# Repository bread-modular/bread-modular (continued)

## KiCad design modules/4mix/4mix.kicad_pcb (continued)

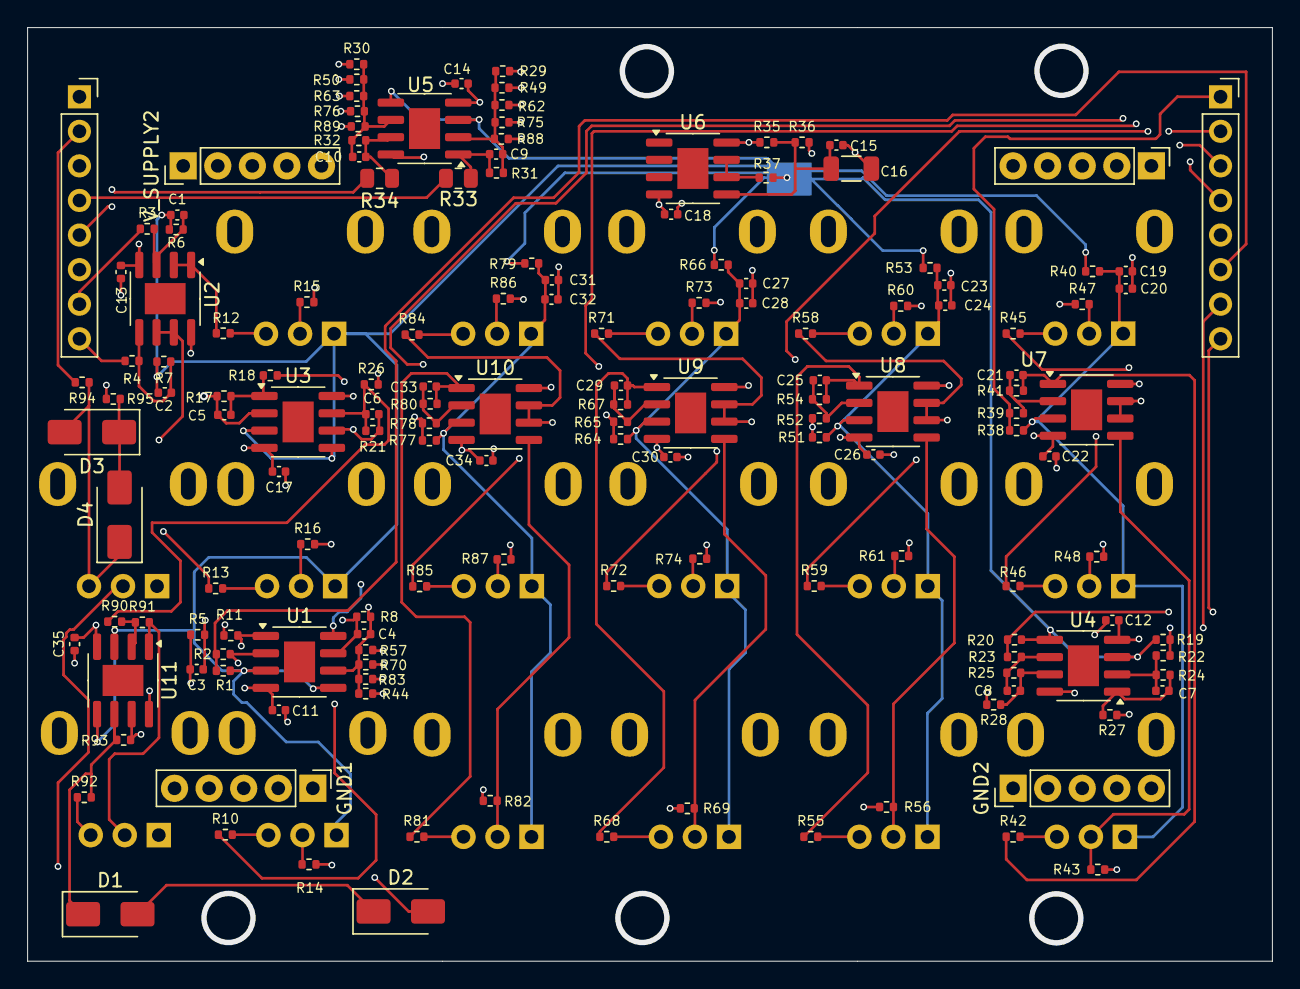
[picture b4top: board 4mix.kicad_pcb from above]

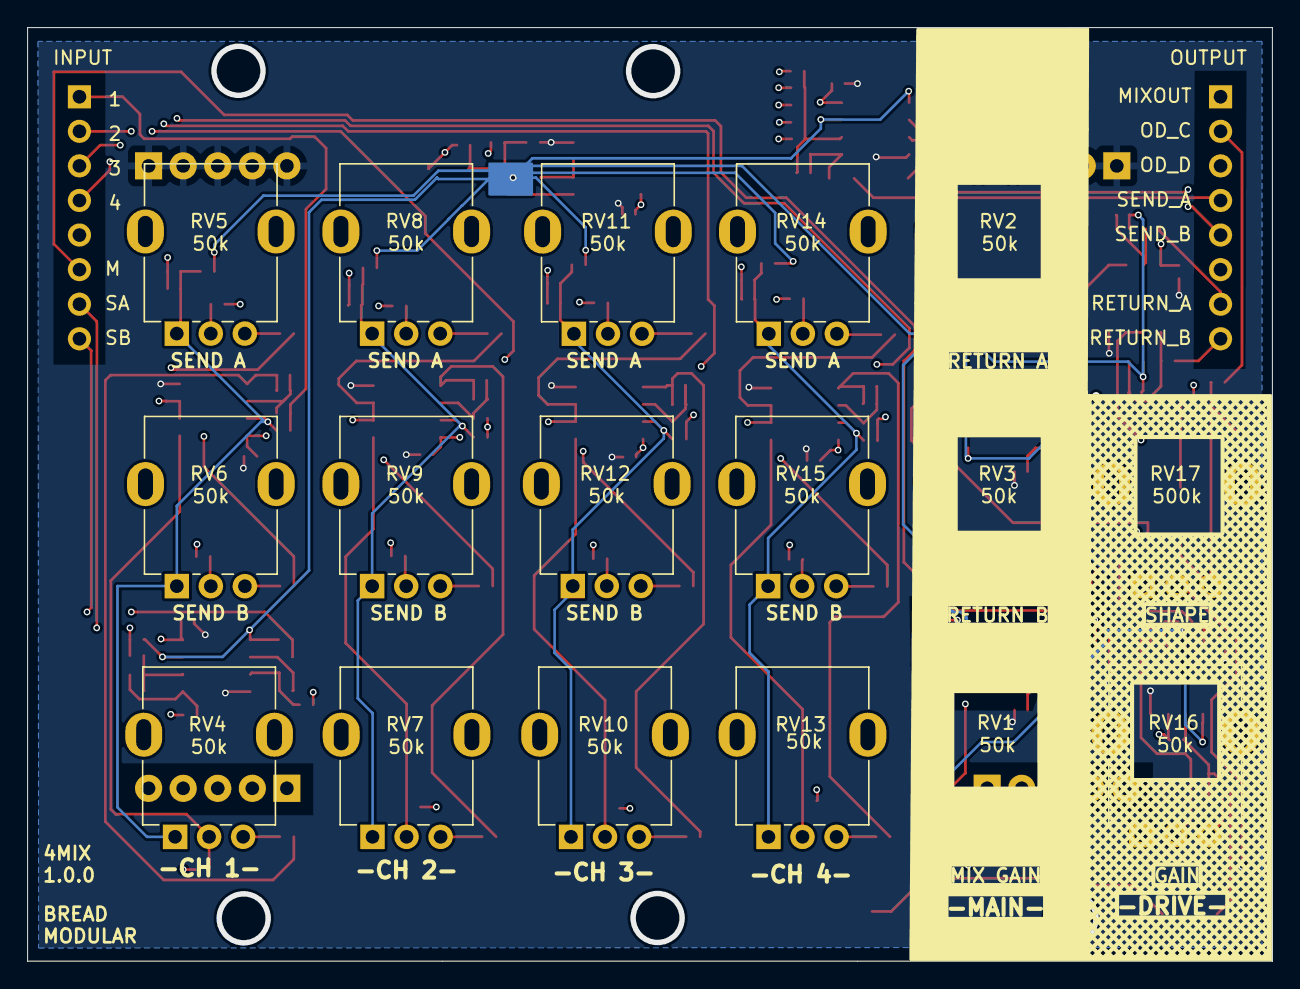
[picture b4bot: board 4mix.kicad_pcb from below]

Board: 4 copper layers, 91.4 x 68.6 mm, 167 parts (17 on the bottom side), 107 nets.

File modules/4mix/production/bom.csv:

Designator,Footprint,Quantity,Value,LCSC Part #
"C1, C2",0402,2,100pf,
"C10, C21, C25, C29, C3, C33, C4, C5, C6, C7, C8, C9",0402,12,47pf,
"C11, C12, C13, C14, C15, C17, C18, C20, C22, C24, C26, C28, C30, C32, C34, C35",0402,16,0.1uf,
C16,1206,1,100uf,
"C19, C23, C27, C31",0402,4,10uf,
"D1, D2, D3",D_SMA,3,SS14,
D4,D_SMA,1,SS210,
"GND1, GND2, V_SUPPLY1, V_SUPPLY2",Power_Connector,4,Conn_01x05_Pin,
"INPUT1, OUTPUT1",PinSocket_1x08_P2.54mm_Vertical,2,Conn_01x05_Socket,
"R1, R19, R20, R38, R51, R6, R64, R7, R77",0402,9,1M,
"R10, R12, R13, R27, R28, R40, R42, R43, R45, R46, R47, R48, R53, R55, R56, R58, R59, R60, R61, R66, R68, R69, R71, R72, R73, R74, R79, R81, R82, R84, R85, R86, R87",0402,33,100,
"R11, R14, R15, R16, R17, R18, R2, R21, R22, R23, R24, R25, R29, R30, R31, R32, R39, R41, R44, R49, R5, R50, R52, R54, R57, R62, R63, R65, R67, R70, R75, R76, R78, R8, R80, R83, R88, R89",0402,38,56k,
"R26, R92, R94, R95",0402,4,1k,
"R3, R35, R36, R4",0402,4,10k,
"R33, R34",0805,2,330,
R37,0402,1,10,
"R90, R91",0402,2,100k,
R93,0402,1,51k,
"RV1, RV10, RV11, RV12, RV13, RV14, RV15, RV16, RV2, RV3, RV4, RV5, RV6, RV7, RV8, RV9",Potentiometer_RV09,16,50k,
RV17,Potentiometer_RV09,1,500k,
"U1, U10, U11, U2, U3, U4, U5, U6, U7, U8, U9",SOIC-8-1EP_3.9x4.9mm_P1.27mm_EP2.29x3mm,11,MCP6002-xSN,

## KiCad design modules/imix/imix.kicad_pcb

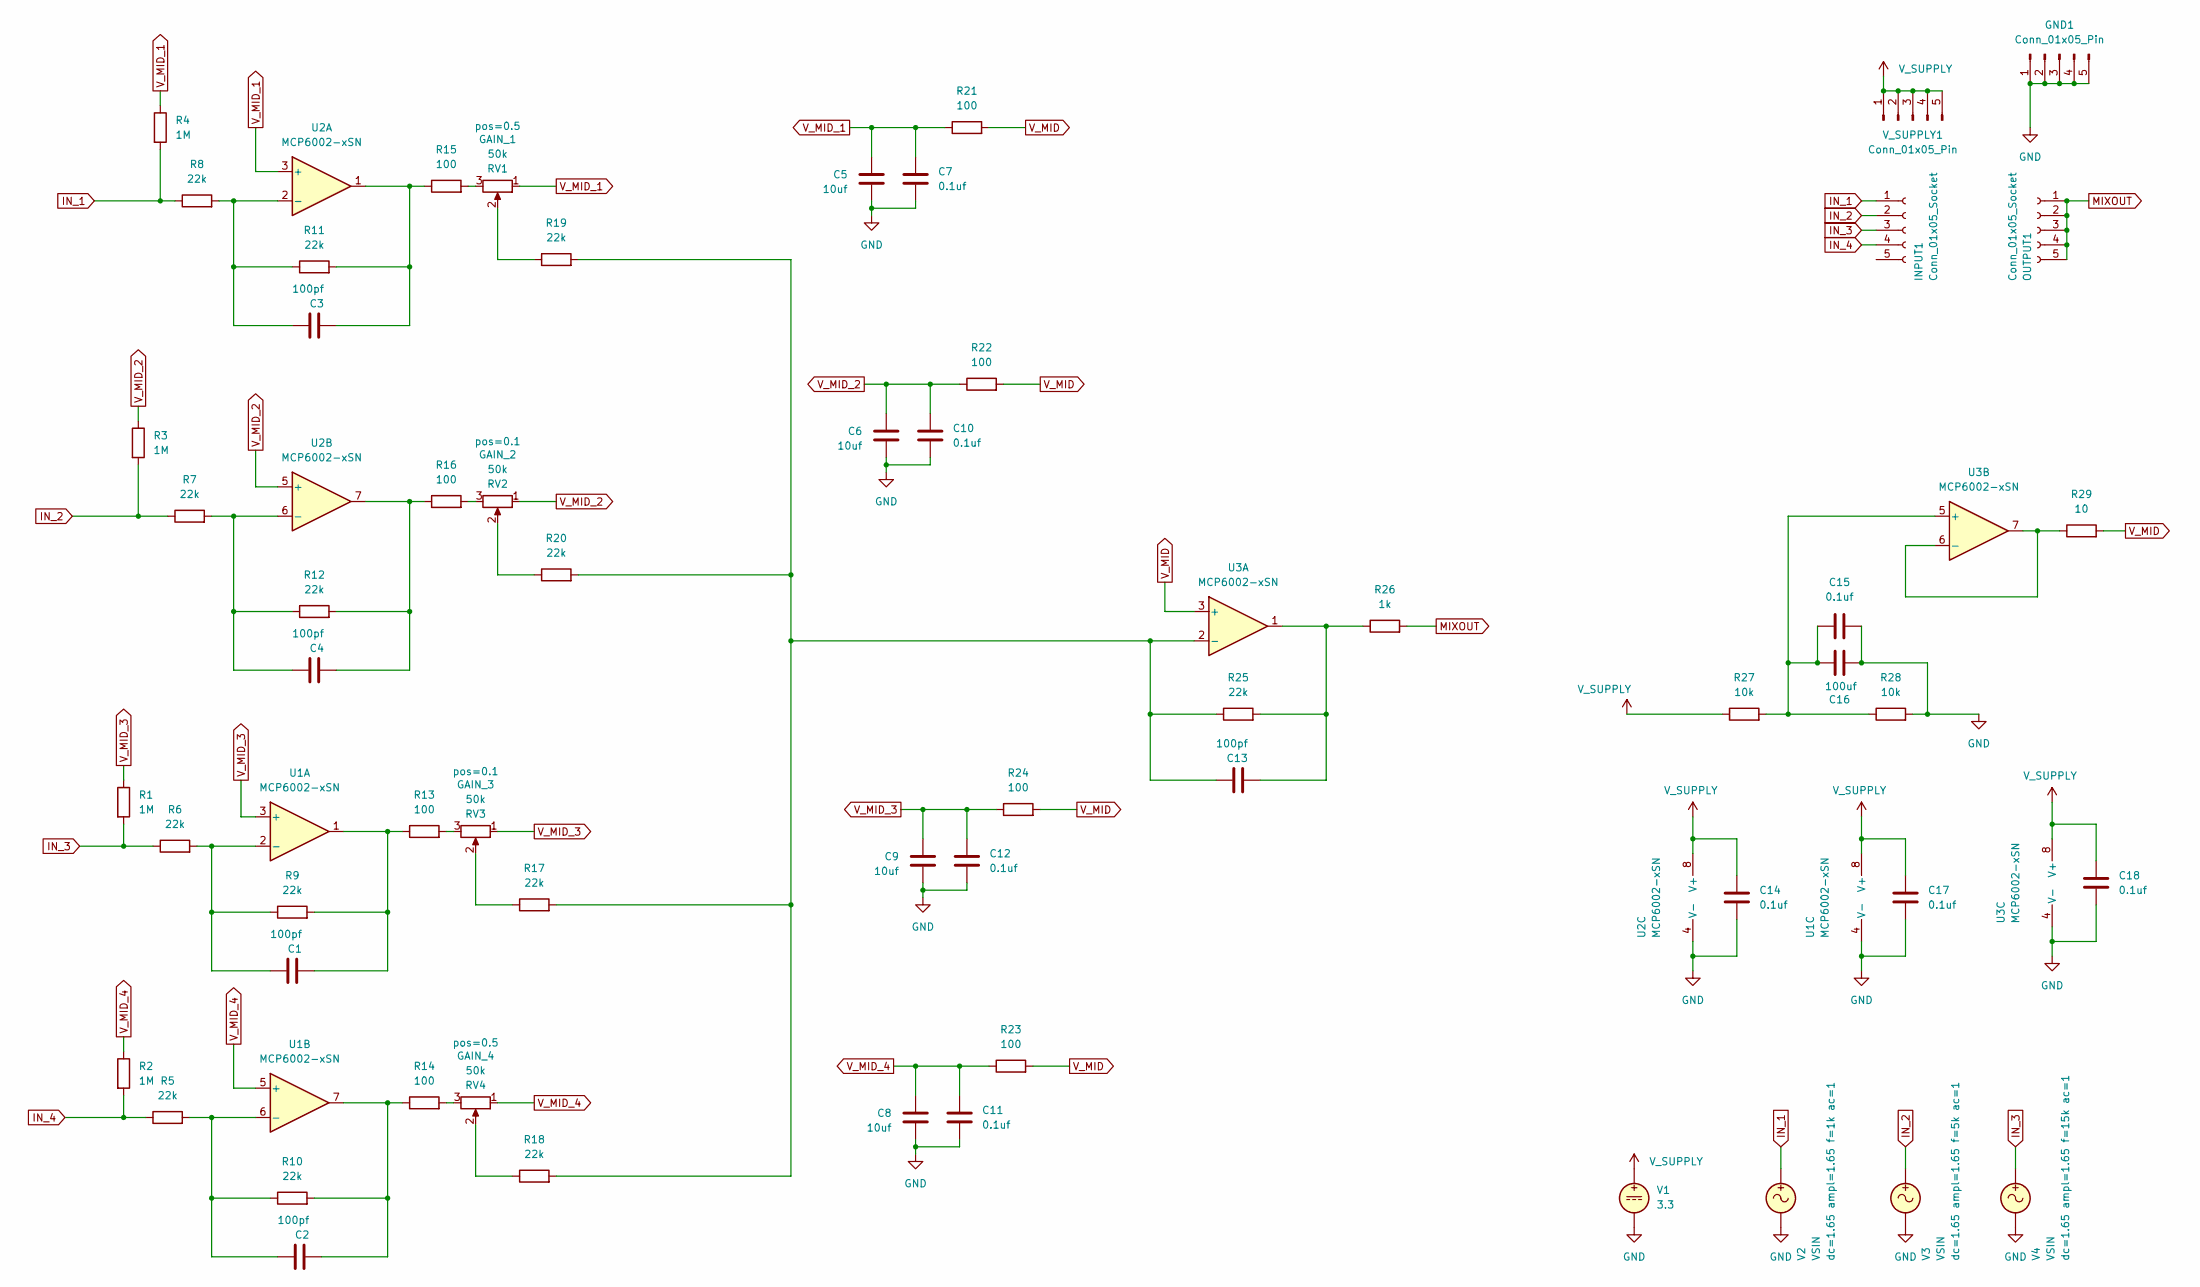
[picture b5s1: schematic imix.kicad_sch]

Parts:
C1, C2, C3, C4, C13: 100pf; C_0402_1005Metric
C5, C6, C8, C9: 10uf; C_0402_1005Metric
C7, C10, C11, C12, C14, C15, C17, C18: 0.1uf; C_0402_1005Metric
C16: 100uf; C_1206_3216Metric
GND1: Conn_01x05_Pin; Power_Connector
INPUT1: Conn_01x05_Socket; PinSocket_1x05_P2.54mm_Vertical
OUTPUT1: Conn_01x05_Socket; PinSocket_1x05_P2.54mm_Vertical
R1, R2, R3, R4: 1M; R_0402_1005Metric
R5, R6, R7, R8, R9, R10, R11, R12, R17, R18, R19, R20, R25: 22k; R_0402_1005Metric
R13, R14, R15, R16, R21, R22, R23, R24: 100; R_0402_1005Metric
R26: 1k; R_0402_1005Metric
R27, R28: 10k; R_0402_1005Metric
R29: 10; R_0402_1005Metric
RV1, RV2, RV3, RV4: 50k; Potentiometer_RV09
U1, U2, U3: MCP6002-xSN; SOIC-8-1EP_3.9x4.9mm_P1.27mm_EP2.29x3mm
V1: 3.3
V2, V3, V4: VSIN
V_SUPPLY1: Conn_01x05_Pin; Power_Connector

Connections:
GND: C5.2, C6.2, C7.2, C8.2, C9.2, C10.2, C11.2, C12.2, C14.2, C15.2, C16.2, C17.2, C18.2, GND1.1, GND1.2, GND1.3, GND1.4, GND1.5, R28.2, U1.4 (V-), U2.4 (V-), U3.4 (V-), V1.2, V2.2, V3.2, V4.2
IN_1: INPUT1.1, R4.2, R8.1, V2.1
IN_2: INPUT1.2, R3.2, R7.1, V3.1
IN_3: INPUT1.3, R1.2, R6.1, V4.1
IN_4: INPUT1.4, R2.2, R5.1
MIXOUT: OUTPUT1.1, OUTPUT1.2, OUTPUT1.3, OUTPUT1.4, OUTPUT1.5, R26.2
unnamed: C1.2, R9.2, R13.1, U1.1
unnamed: C2.2, R10.2, R14.1, U1.7
unnamed: C3.2, R11.2, R15.1, U2.1
unnamed: C4.2, R12.2, R16.1, U2.7
unnamed: C13.2, R25.2, R26.1, U3.1
unnamed: R13.2, RV3.3
unnamed: R14.2, RV4.3
unnamed: R15.2, RV1.3
unnamed: R16.2, RV2.3
unnamed: R17.1, RV3.2
unnamed: R18.1, RV4.2
unnamed: R19.1, RV1.2
unnamed: R20.1, RV2.2
unnamed: C1.1, R6.2, R9.1, U1.2 (-)
unnamed: C2.1, R5.2, R10.1, U1.6 (-)
unnamed: C3.1, R8.2, R11.1, U2.2 (-)
unnamed: C4.1, R7.2, R12.1, U2.6 (-)
unnamed: C13.1, R17.2, R18.2, R19.2, R20.2, R25.1, U3.2 (-)
unnamed: C15.1, C16.1, R27.2, R28.1, U3.5 (+)
unnamed: R29.1, U3.6 (-), U3.7
V_MID: R21.2, R22.2, R23.2, R24.2, R29.2, U3.3 (+)
V_MID_1: C5.1, C7.1, R4.1, R21.1, RV1.1, U2.3 (+)
V_MID_2: C6.1, C10.1, R3.1, R22.1, RV2.1, U2.5 (+)
V_MID_3: C9.1, C12.1, R1.1, R24.1, RV3.1, U1.3 (+)
V_MID_4: C8.1, C11.1, R2.1, R23.1, RV4.1, U1.5 (+)
V_SUPPLY: C14.1, C17.1, C18.1, R27.1, U1.8 (V+), U2.8 (V+), U3.8 (V+), V1.1, V_SUPPLY1.1, V_SUPPLY1.2, V_SUPPLY1.3, V_SUPPLY1.4, V_SUPPLY1.5

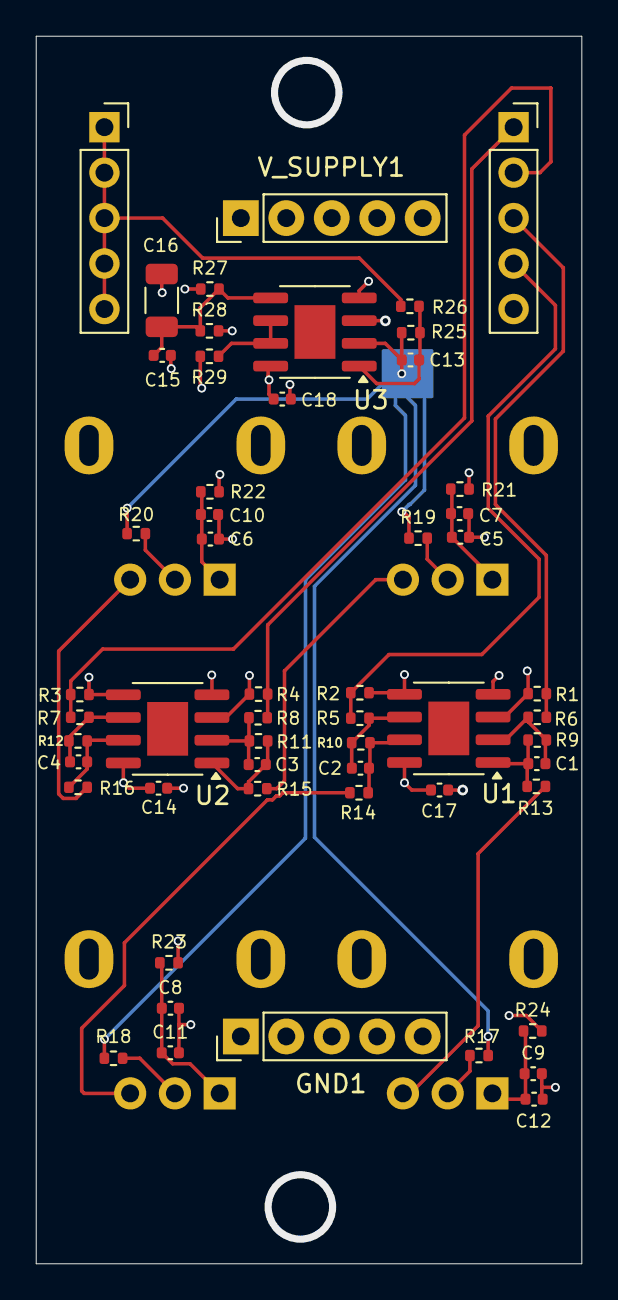
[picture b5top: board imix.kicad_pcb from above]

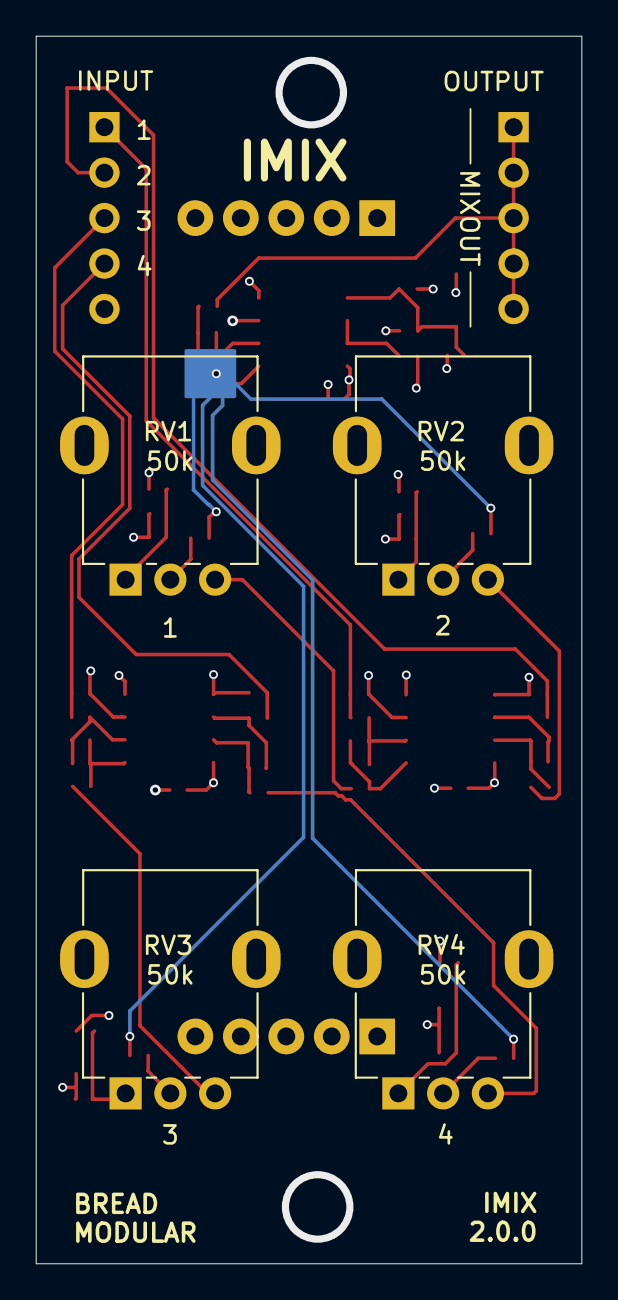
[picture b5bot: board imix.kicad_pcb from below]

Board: 4 copper layers, 30.5 x 68.6 mm, 58 parts (4 on the bottom side), 32 nets.

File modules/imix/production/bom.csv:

Designator,Footprint,Quantity,Value,LCSC Part #
"C1, C13, C2, C3, C4",0402,5,100pf,
"C10, C11, C12, C14, C15, C17, C18, C7",0402,8,0.1uf,
C16,1206,1,100uf,
"C5, C6, C8, C9",0402,4,10uf,
"GND1, V_SUPPLY1",Power_Connector,2,Conn_01x05_Pin,
"INPUT1, OUTPUT1",PinSocket_1x05_P2.54mm_Vertical,2,Conn_01x05_Socket,
"R1, R2, R3, R4",0402,4,1M,
"R10, R11, R12, R17, R18, R19, R20, R25, R5, R6, R7, R8, R9",0402,13,22k,
"R13, R14, R15, R16, R21, R22, R23, R24",0402,8,100,
R26,0402,1,1k,
"R27, R28",0402,2,10k,
R29,0402,1,10,
"RV1, RV2, RV3, RV4",Potentiometer_RV09,4,50k,
"U1, U2, U3",SOIC-8-1EP_3.9x4.9mm_P1.27mm_EP2.29x3mm,3,MCP6002-xSN,

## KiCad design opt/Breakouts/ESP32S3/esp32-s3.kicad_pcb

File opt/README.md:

# KiCad footprint libraries

`fp-lib-table` is the single project-specific footprint library table for all
Bread Modular KiCad projects, including deprecated modules and breakout boards.
Edit it here, not separately in each project. Existing library nicknames are
preserved, including the historical `BreadModular_Panalize` spelling and the
RP2350 breakout's `RP2350_60QFN_minimal` library.

Each project directory contains two **relative symlinks**:

- `fp-lib-table` → this shared `opt/fp-lib-table` file.
- `footprints` → `opt/footprints`, a directory of symlinks to the actual libraries.

The table uses `${KIPRJMOD}/footprints/<library>.pretty`. The `footprints` link
makes this work at any project depth without hard-coded checkout paths or
machine-wide KiCad environment variables. Linking to the library-only directory
also avoids directory cycles through the projects under `opt/Breakouts`.
Standard KiCad libraries continue to come from KiCad's global library table.
Custom symbol-library configuration is unchanged.

## Workspace setup

`workspace_init.sh /path/to/original/checkout` copies **all** submodules listed in
`.gitmodules`, including the four footprint-library submodules and the firmware
library. Tracked libraries and symlinks already arrive with the Git worktree.

- Setup never clones, fetches, or falls back to the network.
- Each copy includes private Git metadata and objects; no hardlinks or Git links
  back to the original checkout are used. Local source changes are copied too.
- Rerunning setup leaves initialized destinations (and their edits) untouched.
- Missing source checkouts or nonempty uninitialized destinations fail with an
  actionable error rather than fetching or overwriting files.
- Sources must be ordinary initialized submodules, not linked worktrees or
  repositories borrowing objects via Git alternates.

On a fresh main checkout, explicitly initialize submodules once before creating
workspaces: `git submodule update --init --recursive`. This manual bootstrap may
access the network; workspace creation itself does not.

## Adding a project

Create both symlinks next to its `.kicad_pro` file, adjusting the relative paths
for its depth. For example, from the repository root:

```sh
ln -s ../../opt/fp-lib-table modules/new-module/fp-lib-table
ln -s ../../opt/footprints modules/new-module/footprints
```

To add a library, add its symlink under `opt/footprints` and its entry to
`opt/fp-lib-table`. Existing projects immediately share the new entry. Reopen
KiCad if it has cached the old library table.

## Verification

From the repository root, with local submodules initialized:

```sh
python3 tests/test_workspace_init.py
# Optional: test copying the original checkout's .git-file-based submodules.
python3 tests/test_workspace_init.py /path/to/original/checkout

# Use a Python interpreter with KiCad's pcbnew module installed.
/usr/bin/python3 tests/check_kicad_libraries.py --drc
```

The workspace tests forbid Git transports and check independent copies,
relocation, rerun safety, and failure cases. The KiCad check verifies every
project link and custom footprint reference, loads the library footprints with
KiCad, and optionally checks every board for missing/unloadable shared libraries
via `kicad-cli`. Global-library footprint issues are reported separately; they
and unrelated existing PCB design-rule violations do not fail the shared-library
check. Projects without a PCB or generated by a newer KiCad major version than
the installed CLI are explicitly skipped for board DRC; their shared-library
paths and footprint loads are still checked.

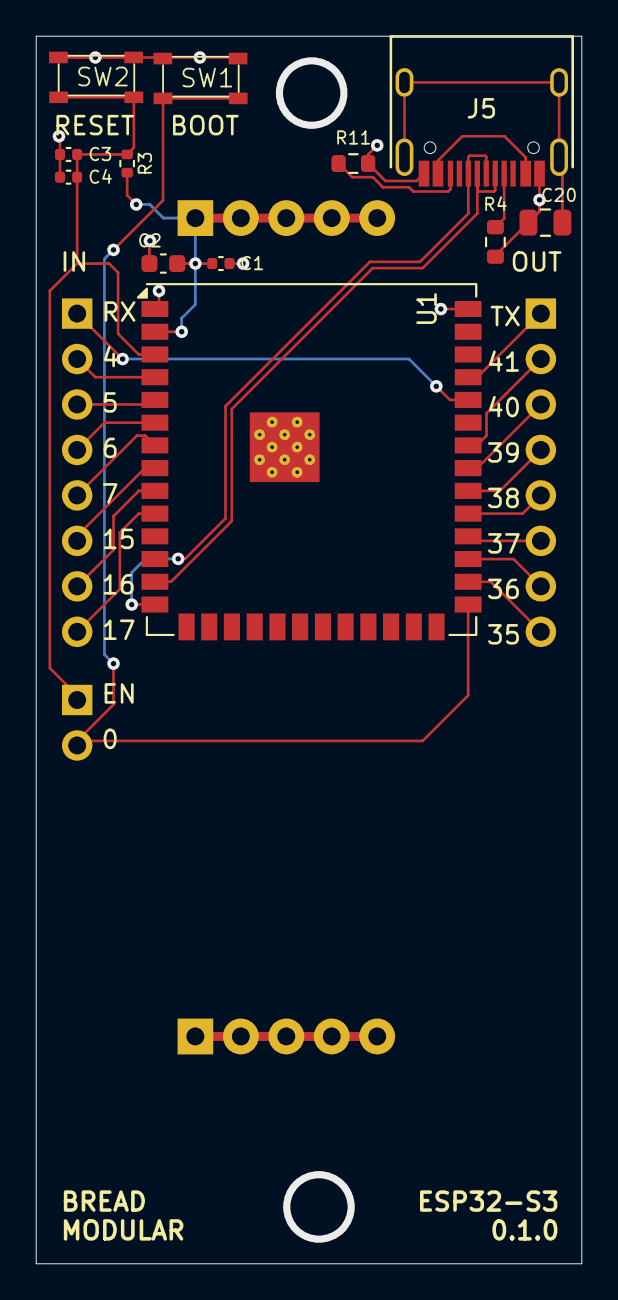
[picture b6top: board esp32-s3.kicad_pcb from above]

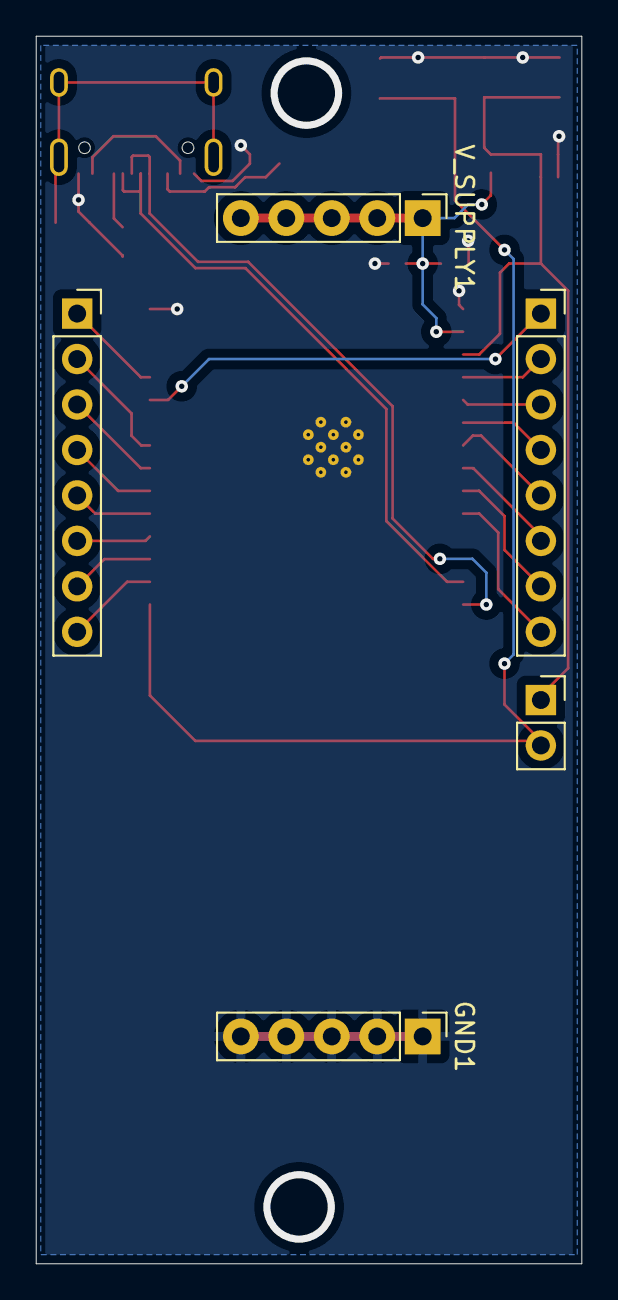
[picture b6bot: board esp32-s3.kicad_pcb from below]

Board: 2 copper layers, 30.5 x 68.6 mm, 17 parts (5 on the bottom side), 26 nets.

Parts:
C1, C4: 0.1uf; C_0402_1005Metric
C2: 22uf; C_0603_1608Metric
C3: 1uf; C_0402_1005Metric
C20: 10nf; C_0805_2012Metric
GND1: Conn_01x05_Pin; Power_Connector
INPUT1: Conn_01x08_Socket; PinSocket_1x08_P2.54mm_Vertical
INPUT2: Conn_01x02_Socket; PinSocket_1x02_P2.54mm_Vertical
J5: USB_C_Receptacle_USB2.0_14P; HRO-TYPE-C-31-M-12
OUTPUT1: Conn_01x08_Socket; PinSocket_1x08_P2.54mm_Vertical
R3: 10k; R_0402_1005Metric
R4, R11: 5.1k; R_0603_1608Metric
SW1, SW2: K2-1808SN-A4SW-01
U1: ESP32-S3-WROOM-1U-N16R8; ESP32-S3-WROOM-1U
V_SUPPLY1: Conn_01x05_Pin; Power_Connector

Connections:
EN: C3.2, C4.2, INPUT2.1, R3.2, SW2.2 (B), U1.3 (EN)
GND: C1.2, C2.2, C3.1, C4.1, C20.2, GND1.1, GND1.2, GND1.3, GND1.4, GND1.5, J5.A1 (GND), J5.A12 (GND), R4.2, R11.2, SW1.1 (A), SW2.1 (A), U1.1 (GND), U1.40 (GND), U1.41 (GND)
IO0: INPUT2.2, SW1.2 (B), U1.27 (IO0)
IO4: INPUT1.2, U1.4 (IO4)
IO5: INPUT1.3, U1.5 (IO5)
IO6: INPUT1.4, U1.6 (IO6)
IO7: INPUT1.5, U1.7 (IO7)
IO15: INPUT1.6, U1.8 (IO15)
IO16: INPUT1.7, U1.9 (IO16)
IO17: INPUT1.8, U1.10 (IO17)
IO35: OUTPUT1.8, U1.28 (IO35)
IO36: OUTPUT1.7, U1.29 (IO36)
IO37: OUTPUT1.6, U1.30 (IO37)
IO38: OUTPUT1.5, U1.31 (IO38)
IO39: OUTPUT1.4, U1.32 (IO39)
IO40: OUTPUT1.3, U1.33 (IO40)
IO41: OUTPUT1.2, U1.34 (IO41)
unnamed: J5.A5 (CC1), R4.1
unnamed: J5.B5 (CC2), R11.1
unnamed: C20.1, J5.S1 (SHIELD)
unnamed: J5.A4 (VBUS), J5.A9 (VBUS)
RX: INPUT1.1, U1.36 (RXD0)
TX: OUTPUT1.1, U1.37 (TXD0)
USB_D+: J5.A6 (D+), J5.B6 (D+), U1.14 (USB_D+)
USB_D-: J5.A7 (D-), J5.B7 (D-), U1.13 (USB_D-)
V_SUPPLY: C1.1, C2.1, R3.1, U1.2 (3V3), V_SUPPLY1.1, V_SUPPLY1.2, V_SUPPLY1.3, V_SUPPLY1.4, V_SUPPLY1.5

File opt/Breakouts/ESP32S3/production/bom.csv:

Designator,Footprint,Quantity,Value,LCSC Part #
"C1, C4",0402,2,0.1uf,
C2,0603,1,22uf,
C20,0805,1,10nf,
C3,0402,1,1uf,
"GND1, V_SUPPLY1",Power_Connector,2,Conn_01x05_Pin,
"INPUT1, OUTPUT1",PinSocket_1x08_P2.54mm_Vertical,2,Conn_01x08_Socket,
INPUT2,PinSocket_1x02_P2.54mm_Vertical,1,Conn_01x02_Socket,
J5,HRO-TYPE-C-31-M-12,1,USB_C_Receptacle_USB2.0_14P,
"R11, R4",0603,2,5.1k,
R3,0402,1,10k,
"SW1, SW2",K2-1808SN-A4SW-01,2,K2-1808SN-A4SW-01,
U1,ESP32-S3-WROOM-1U,1,ESP32-S3-WROOM-1U-N16R8,

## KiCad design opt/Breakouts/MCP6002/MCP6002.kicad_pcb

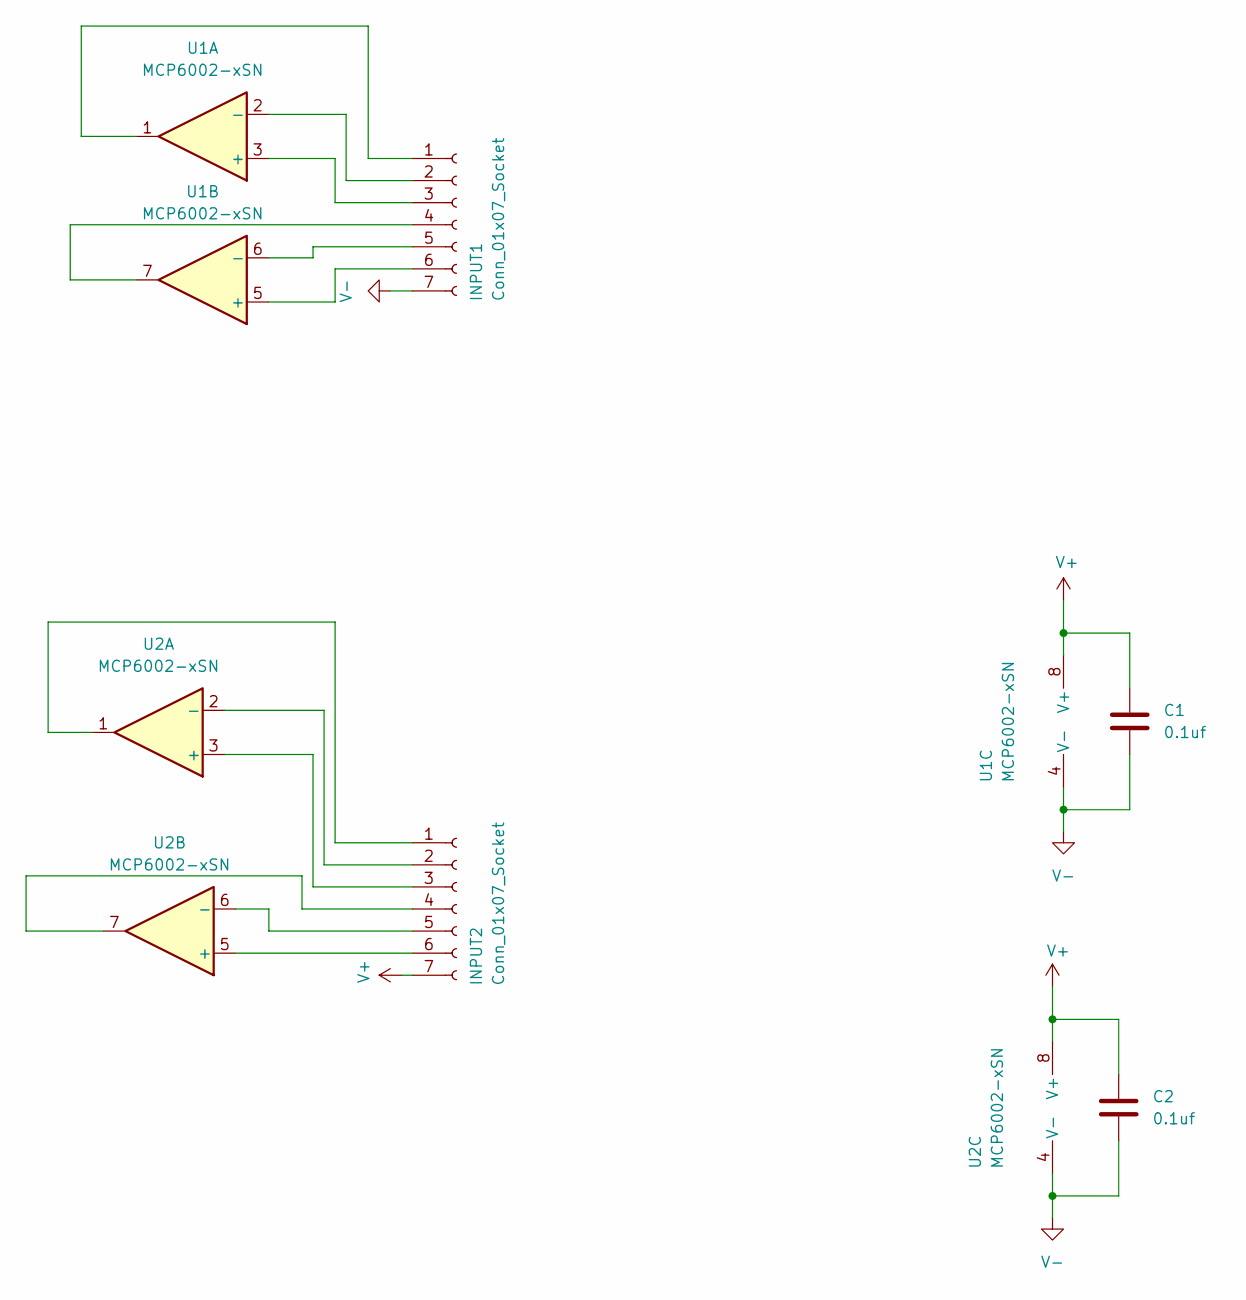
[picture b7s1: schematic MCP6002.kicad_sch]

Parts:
C1, C2: 0.1uf; C_0402_1005Metric
INPUT1, INPUT2: Conn_01x07_Socket; PinSocket_1x07_P2.54mm_Vertical
U1, U2: MCP6002-xSN; SOIC-8-1EP_3.9x4.9mm_P1.27mm_EP2.29x3mm

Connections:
unnamed: INPUT1.1, U1.1
unnamed: INPUT1.2, U1.2 (-)
unnamed: INPUT1.3, U1.3 (+)
unnamed: INPUT1.4, U1.7
unnamed: INPUT1.5, U1.6 (-)
unnamed: INPUT1.6, U1.5 (+)
unnamed: INPUT2.1, U2.1
unnamed: INPUT2.2, U2.2 (-)
unnamed: INPUT2.3, U2.3 (+)
unnamed: INPUT2.4, U2.7
unnamed: INPUT2.5, U2.6 (-)
unnamed: INPUT2.6, U2.5 (+)
V+: C1.1, C2.1, INPUT2.7, U1.8 (V+), U2.8 (V+)
V-: C1.2, C2.2, INPUT1.7, U1.4 (V-), U2.4 (V-)

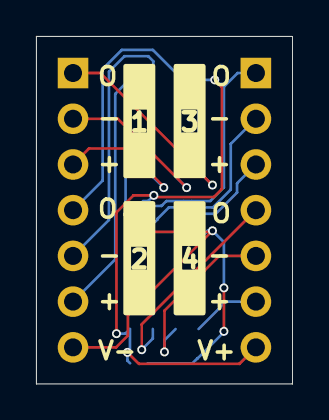
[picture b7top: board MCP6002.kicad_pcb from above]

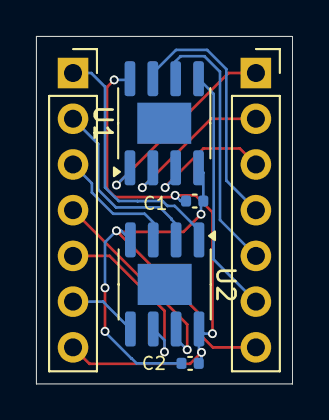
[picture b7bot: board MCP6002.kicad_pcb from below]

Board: 2 copper layers, 14.2 x 19.3 mm, 6 parts (6 on the bottom side), 14 nets.

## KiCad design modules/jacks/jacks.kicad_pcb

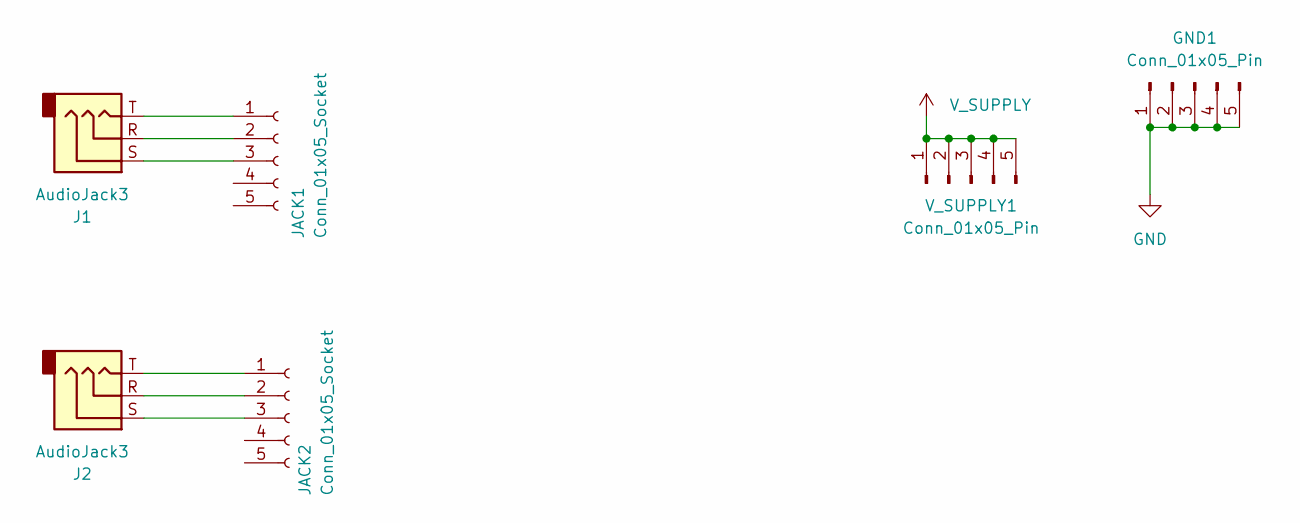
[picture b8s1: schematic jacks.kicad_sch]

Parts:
GND1: Conn_01x05_Pin; Power_Connector
J1, J2: AudioJack3; Jack_3.5mm_QingPu_WQP-PJ366ST_Vertical
JACK1, JACK2: Conn_01x05_Socket; PinSocket_1x05_P2.54mm_Vertical
V_SUPPLY1: Conn_01x05_Pin; Power_Connector

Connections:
GND: GND1.1, GND1.2, GND1.3, GND1.4, GND1.5
unnamed: J1.T, JACK1.1
unnamed: J1.R, JACK1.2
unnamed: J1.S, JACK1.3
unnamed: J2.T, JACK2.1
unnamed: J2.R, JACK2.2
unnamed: J2.S, JACK2.3
V_SUPPLY: V_SUPPLY1.1, V_SUPPLY1.2, V_SUPPLY1.3, V_SUPPLY1.4, V_SUPPLY1.5

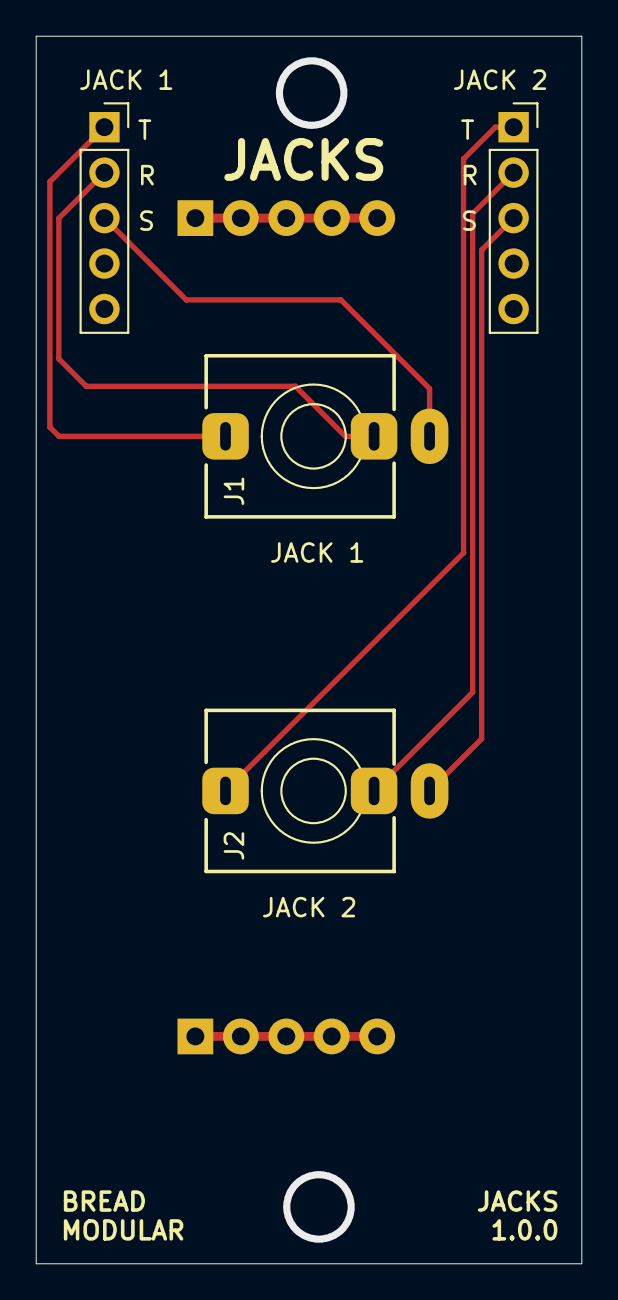
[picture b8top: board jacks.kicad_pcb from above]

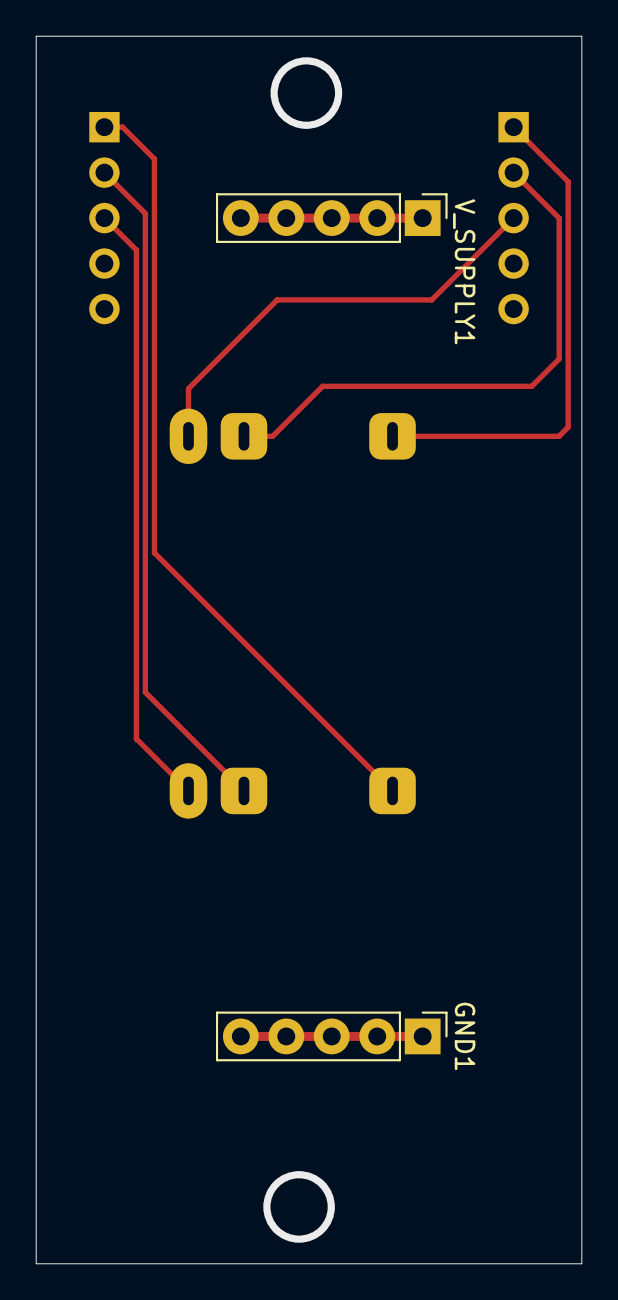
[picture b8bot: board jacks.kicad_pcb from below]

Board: 2 copper layers, 30.5 x 68.6 mm, 6 parts (2 on the bottom side), 8 nets.

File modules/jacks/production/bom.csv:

Designator,Footprint,Quantity,Value,LCSC Part #
"GND1, V_SUPPLY1",Power_Connector,2,Conn_01x05_Pin,
"J1, J2",Jack_3.5mm_QingPu_WQP-PJ366ST_Vertical,2,AudioJack3,
"JACK1, JACK2",PinSocket_1x05_P2.54mm_Vertical,2,Conn_01x05_Socket,

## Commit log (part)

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2025-06-17 For metalverb, it doesn't work with BPM changes. In that, we set the param 1 as millisecond values instead of beats. Which allow us to keep the same sound signature across all the BPM ranges.
2025-06-17 16bit_1.2.0
2025-06-18 Add initial version of 16bit_e2e
2025-06-18 Add better send_and_receive function
2025-06-18 Add order test tests
2025-06-18 Ad MIDI sending as well
2025-06-18 Add the MIDI coonnection on the top
2025-06-19 Add a way to record an audio from a MIDI input and record it verify it againts a reference
2025-06-19 Change directory names
2025-06-25 4mix: Fix leaky ch1 sendA routing Also change the mounting hole positions to match mirroring
2025-06-25 4mix_0.3.0
2025-06-26 16bit: Fix enevelop not functioning well issue in the polysynth app
2025-06-26 16bit_1.2.1
2025-06-26 Add breakout: HCPL-063L
2025-06-27 mcc: make sure bank selection persists Due to some EEPROM issues, sometimes MCC switch the bank to different values. This impacts a lot to the functionality. Now we fixed it with redundant EEPROM val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
2025-06-27 mcc_1.0.1
2025-07-03 pots: initial release
2025-07-03 pots_1.0.0
2025-07-03 Remove rv_base module since now we have pots
2025-07-03 jacks: initial release
2025-07-03 jacks_1.0.0
2025-07-03 Add MCP6002 breakout
2025-07-05 env: Introduce MIDI_VELOCITY mode With that, velocity will modulate the CV2. This way, we can easily implement accent support.
2025-07-05 env_1.2.0
2025-07-10 4mix: Fixing ch4 send-b leakage.
2025-07-10 4mix_0.4.0
2025-07-13 Remove old DAC from the 16bit+
2025-07-13 Detect 16bit+ at runtime via IO21
2025-07-14 Finalize the schematics
2025-07-14 finalize audio codec routing
2025-07-14 Finalize all the routing
2025-07-14 Add 16bit+ production code
2025-07-14 16bit+_0.1.0
2025-07-15 Add elab app
2025-07-15 Add super-saw to the A2
2025-07-15 16bit mode button is a trigger generator
2025-07-15 Add a pulse generator too.
2025-07-16 Set pulse gen max freq to 30
2025-07-20 Add support to send binary data over the web-serial
2025-07-21 capturing and sending samples over webserial
2025-07-22 Sampling ADC
2025-07-22 Improve memory allocation
2025-07-22 16bit_1.3.0
2025-08-10 Add some improvements to 4mix
2025-08-13 Finished the new schematic for 4mix
2025-08-13 Reconfigure the simulations
2025-08-13 Add base setup for routing
2025-08-13 Implement channel 1 routing
2025-08-13 Routed channel 2
2025-08-14 add channel 3 routing
2025-08-14 Added channel 4
2025-08-14 Add vmid routing
2025-08-14 Add routes for mian mix
2025-08-15 Add sends routing
2025-08-15 Complete sends routing
2025-08-16 Add return buffering
2025-08-16 Finalized main routing of the board
2025-08-16 Finialize all the routing
2025-08-16 Fix all the routing issues
2025-08-16 Finalized all the routing and ready to fab
2025-08-16 Add 4mix fab data
2025-08-16 4mix_0.5.0
2025-08-22 Update midi and io pins
2025-08-22 Implement ES8388 I2S support
2025-08-22 Add schematics
2025-08-23 Finish adding the breakout
2025-08-29 Replace the LDO for AP212K This has an EN pin so we can add reset support
2025-08-29 Add basic routing
2025-08-29 Add production version
2025-08-29 base_1.2.0
2025-09-02 Move Elab implementation to a it's own cpp file and mark hot & cold functions.
2025-09-02 Move all the AudioApp to it's own .ccp class
2025-09-02 16bit_1.4.0
2025-09-12 env: Add improved EEPROM handling. This produce bettter setting savings for mode buttons
2025-09-13 env_1.2.1
2025-09-22 Add base 32bit project
2025-09-23 Add 32bit schematics
2025-09-23 Finished basic routing
2025-09-23 Finished routing
2025-09-23 Add the production files
2025-09-23 32bit_0.1.0
2025-09-23 4mix: rename as 1.0.0
2025-09-23 4mix_1.0.0
2025-10-08 16bit: Moved CDATA & CCLK labels. They were just being marked wrongly in the ES8388 side
2025-10-08 16bit_0.1.1
2025-10-10 Add a 3.3v island for es8388
2025-10-10 Add better routing for power
2025-10-10 32bit_0.2.0
2025-10-10 Add improved schematics
2025-10-10 Add the initial revered board for layout
2025-10-11 Start placing the PCB
2025-10-11 Finalized routing
2025-10-11 imix_2.0.0
2025-10-13 Add the esp32-template with 240Mhz
2025-10-13 Add the led support
2025-10-13 Add PSRAM support We can access it via heap_caps_malloc
2025-10-14 Added 8bit supersaw detune from CV1 with midi input
2025-10-14 Improved offset calculation
2025-10-14 Introduce the button support
2025-10-14 Add CV support
2025-10-14 Add the initial audio_loop
2025-10-14 Access psram inside the audio loop
2025-10-14 Add more audio_loop examples
2025-10-14 Add some comments
2025-10-14 16bit+: add external crystal to generate MCLK
2025-10-17 Using int16_t for audio processing ES8388 natively uses signed 16bit. So, we should follow it Also implemted a very simple LP-filter using a one sample delay
2025-10-17 Add proper delay example with circular buffer.
2025-10-19 Introduce a ring buffer
2025-10-19 Improve ring buffer lookup function
2025-10-19 Add better clamping support
2025-10-19 process data using floats in the audio loop
2025-10-20 Add simple delay
2025-10-20 Add basic MIDI handling setup
2025-10-20 Add BPM calculations
2025-10-20 Change steady alpha
2025-10-20 Change callback names.
2025-10-20 Reduce the noise level
2025-10-20 Add some noise reduction solutions
2025-10-20 Add param support
2025-10-20 Add feedback delay
2025-10-21 Introduce buffer_size configuration for the audio tools.
2025-10-21 Use PSRAM for the delay buffer
2025-10-21 Add BPM synced delay time control
2025-10-22 Refactor the delay for a single channel
2025-10-22 Add right channel delay
2025-10-22 Add a bypass mode when the MODE button is pressed.
2025-10-22 Refactor params. Clean the code and add what's sound good
2025-10-22 Set the main delay range to half a beat.
2025-10-23 Change delay params based on performance usage
2025-10-23 Introduced the concept of an app
2025-10-23 Refactor some types
2025-10-23 Add host unit tests for shared lib helpers
2025-10-23 Make sure it runs well
2025-10-23 Fix button setup race and ES8388 mute register
2025-10-24 Add basic comb filter for the reverb
2025-10-24 Use floats in the buffer
2025-10-24 Impelement the main comb filter algorithm
2025-10-25 Replaced the logic with our exising utils. It will give us a much cleaner sounding result
2025-10-25 Introduce the struct
2025-10-25 Add init and destroy functionalities
2025-10-25 Add the process function
2025-10-25 Add the comb filter struct
2025-10-27 Add the basic all pass filter implementation
2025-10-27 Hardcode the sample rate. We don't need to change it often. It makes some calculations to make in the compile time.
2025-10-27 Add the all pass filter abstraction
2025-10-28 Add the reverb
2025-10-28 Implement the classic reverb.
2025-10-28 Refactor the audio fx a bit
2025-10-28 Use comb filter in the fx rack
2025-10-28 Add tests for filters
2025-10-29 Add CV1 and CV2 reading support
2025-10-29 Add delay params to CV1 and CV2
2025-10-29 Fix the bypass issue
2025-10-29 Improve the test runner
2025-10-30 Add delay pipe option
2025-10-30 Add persistant functionality too
2025-10-30 Refactor button state related logic
2025-10-31 Add MIDI related tests
2025-10-31 Improve tests result UI
2025-10-31 Add CV related tests
2025-10-31 Add test cases for bm_button
2025-11-05 4mix: Align the 5pin socket position correctly
2025-11-05 4mix_1.0.1
2025-11-06 Improve 32bit power supply
2025-11-07 32bit: Use a known ferrite bead
2025-11-07 32bit_0.3.2
2025-11-09 Implement the basic LFO where CV1 controls the frequency
2025-11-09 Add waveform morphing with CV2
2025-11-09 Add support for two complex waveforms
2025-11-09 Add a better curve for the CV1
2025-11-09 Blink the LED according to the lfo
2025-11-09 Add the README
2025-11-09 8bit_1.2.0
2025-11-16 Introduce a installer packager
2025-11-16 Add usb_serial message listning setup
2025-11-16 Add delay->reverb pipe again
2025-11-17 Add the README.md about generating and uploading firmwares
2025-11-17 Add support for compile time multiple apps They will became firmwares when we are building them.
2025-11-17 Add cleaning step after the running the package script
2025-11-17 Allow to get firmware name and version as commands.
2025-11-18 Add support sending values
2025-11-18 Implemented a pipe app
2025-11-21 Use fxrack as the default app
2025-11-21 32bit_1.0.0
2025-11-27 8bit: now LFO firmware update the GATE
2025-11-27 8bit_1.2.1
2025-11-27 Update the LFO readme
2026-01-02 4mix: Fix routing errors related to ch:1 Ch1 is shorting with the 5v So, this fixes it.
2026-01-02 4mix_1.0.2
2026-01-18 Add initial version
2026-01-18 Add basic rumble controls
2026-01-18 Predelay filter
2026-01-18 16bit_1.5.0
2026-01-18 Add missing rumble config to the 16bit
2026-01-18 16bit_1.5.1
2026-01-19 16bit: Fix delay smoothing issue with low fps Delay seems to be not working when the fps values are very low Replace smoothing logic to fix that
2026-01-19 16bit_1.5.2
2026-01-30 Remove 32bit unwanted caps & etc
2026-01-30 Add two LDO approach
2026-01-30 Add the routing
2026-02-05 mcc: Make sure we send CCs at every 1 seconds It was disabled before
2026-02-05 mcc_1.0.2
2026-02-05 Make sure rumble is turned off by default
2026-02-05 16bit_1.5.3
2026-06-06 Add CLI scripts
2026-06-06 Make sure scripts work without in the scripts directory
2026-06-06 Add picotool & deploy without buttons
2026-06-06 Make the delay_fx 4th cc param as a highpass filter
2026-06-06 Add resonance for the delay_fx hf filter We only add resonance after 500Hz to prevent low end boost
2026-06-06 16bit_1.6.0
